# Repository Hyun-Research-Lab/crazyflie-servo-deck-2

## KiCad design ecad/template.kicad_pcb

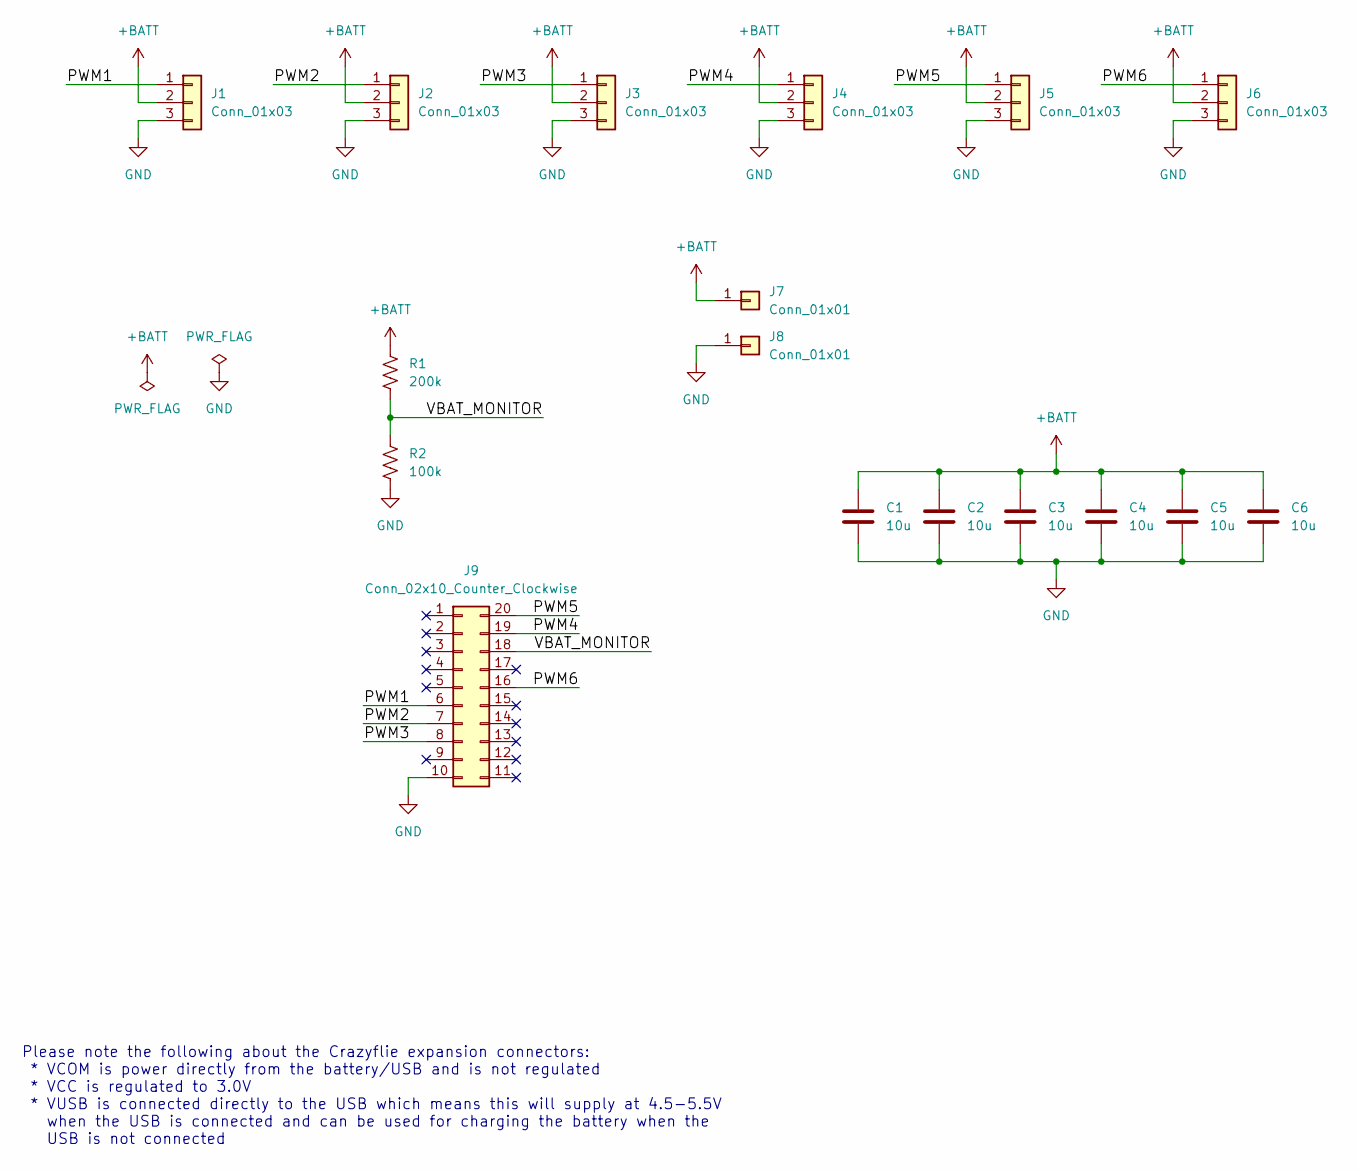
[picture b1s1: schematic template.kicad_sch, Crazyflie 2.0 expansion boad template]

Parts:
C1, C2, C3, C4, C5, C6: 10u; C_0805_2012Metric_Pad1.18x1.45mm_HandSolder
J1, J2, J3, J4, J5, J6: Conn_01x03; PinHeader_1x03_P2.54mm_Horizontal
J7, J8: Conn_01x01; Servo_Power_GND_2.0x1.5mm
J9: Conn_02x10_Counter_Clockwise; Crazyflie_DeckHeader_2x10_P2.00_Vertical
R1: 200k; R_0805_2012Metric_Pad1.20x1.40mm_HandSolder
R2: 100k; R_0805_2012Metric_Pad1.20x1.40mm_HandSolder

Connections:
+BATT: C1.1, C2.1, C3.1, C4.1, C5.1, C6.1, J1.2, J2.2, J3.2, J4.2, J5.2, J6.2, J7.1, R1.1
/PWM1: J1.1, J9.6
/PWM2: J2.1, J9.7
/PWM3: J3.1, J9.8
/PWM4: J4.1, J9.19
/PWM5: J5.1, J9.20
/PWM6: J6.1, J9.16
/VBAT_MONITOR: J9.18, R1.2, R2.1
GND: C1.2, C2.2, C3.2, C4.2, C5.2, C6.2, J1.3, J2.3, J3.3, J4.3, J5.3, J6.3, J8.1, J9.10, R2.2

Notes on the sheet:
Please note the following about the Crazyflie expansion connectors: * VCOM is power directly from the battery/USB and is not regulated * VCC is regulated to 3.0V * VUSB is connected directly to the USB which means this will supply at 4.5-5.5V when the USB is connected and can be used for charging t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

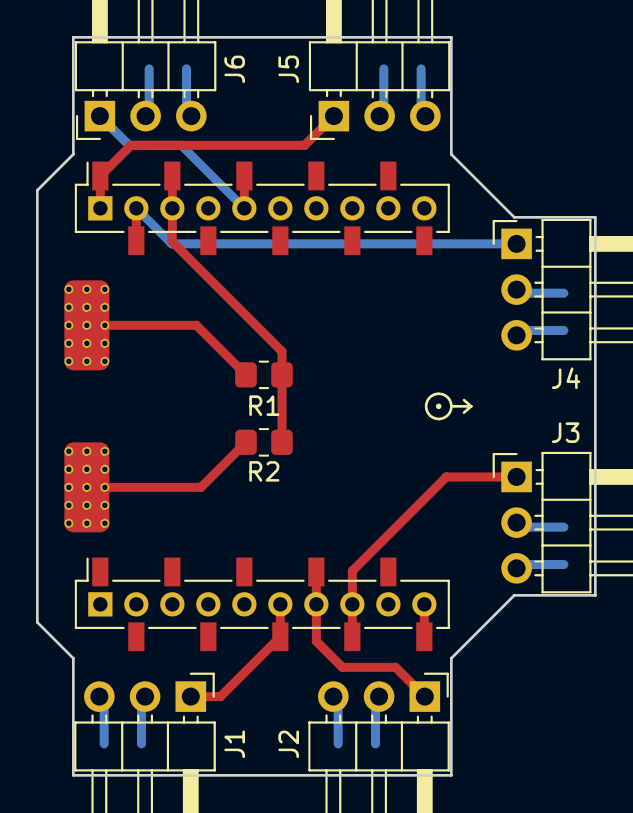
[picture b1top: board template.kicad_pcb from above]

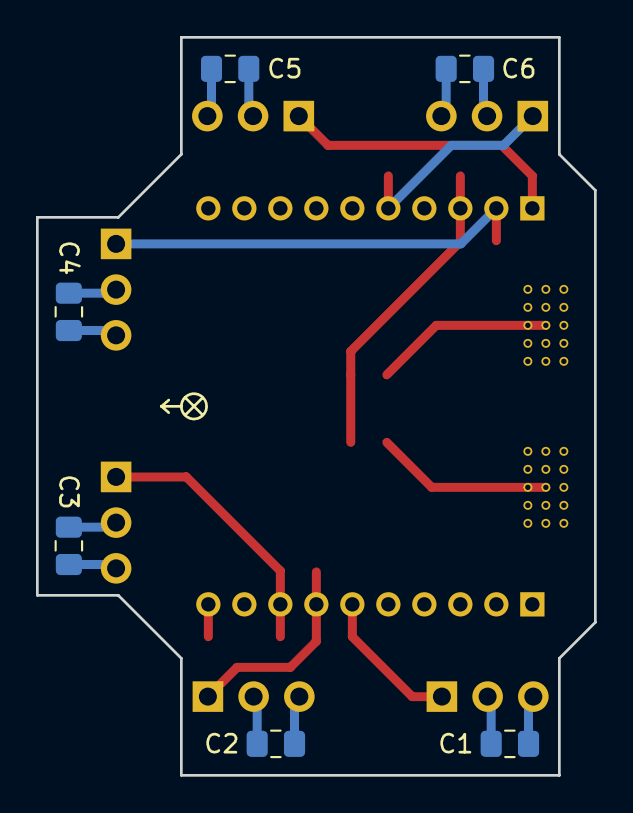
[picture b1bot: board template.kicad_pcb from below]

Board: 4 copper layers, 31.0 x 41.0 mm, 18 parts (6 on the bottom side), 9 nets.

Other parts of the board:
EXP_ORIENTATION: VAL**; EXP_ORIENTATION

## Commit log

2025-09-11 Convert to KiCad 9.0
2025-09-14 Footprints working
2025-09-15 Add power flags
2025-09-20 Routing
2025-09-22 Logan's changes

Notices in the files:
ecad/template.kicad_pcb:
Licensed under CC-BY 4.0
